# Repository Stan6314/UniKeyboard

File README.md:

UniKeyboard - Universal Keyboard
================================

The TinyBasRV and TinyBasRO microcomputers require a keyboard for writing programs and entering data. While the TinyBasRV uses a standard PC keyboard with a PS/2 connector, the TinyBasRO uses a CardKB keyboard designed for the I2C bus.

The keyboard design described here offers an alternative if you encounter any of the following problems:

*  A PS/2 keyboard for TinyBasRV is too large for your intended purpose
*  CardKB is too small (the buttons are too close together)
*  You don't have a PS/2 keyboard and can't seem to find one
*  You have the same problem with CardKB
*  You have TinyBasRV and TinyBasRO microcomputers and would like to use just one keyboard for both of them

A keyboard — for which you can find the technical documentation (circuit diagram and PCB layout) in the KiCad folder — might help you resolve any of the issues mentioned above. The documentation is in version 9.0.

In the `hw_pictures` folder, you will find images for assembling the keyboard. You can mount either 5x5 mm buttons onto the board or (with a bit of skill) 6x6 mm buttons.

The keyboard uses a simple 8-bit microcontroller—the ATtiny414 or ATtiny814—and is designed for a single-sided printed circuit board. You can connect it via an HY2.0-4P Grove connector or a 4-pin female header. Alternatively, you can populate the board with both connectors:

The source code for programming the microcontroller's FLASH memory can be found in the `src` folder. It contains source programs for both Arduino (with the `megaTinyCore` library installed) and the standalone AVR-GCC compiler.

Once the microcontroller's FLASH memory has been programmed, the keyboard will operate in one of three modes:

------------------------------------------
1) UART keypad (flashes blue upon startup)

If you connect the output connector as shown in the illustration 

The keyboard will transmit data like a UART transmitter at a speed of 9600 baud, 8 bits, no parity. It can be used in various devices for entering data and commands.

----------------------------------------
2) I2C keypad (flashes red upon startup)

When connecting the keyboard according to 

the keyboard will behave like a CardKB for TinyBasRO.

---------------------------------------------
3) PS/2 keyboard (flashes green upon startup)

When connected according to the diagram and with the short R43 on the printed circuit board connected:

The keyboard will operate in PS/2 mode for TinyBasRV. Please note that in this mode, it does not respond to the initial query from the PC during the BIOS self-test. If connected to a PC, it would only establish communication if the original keyboard were removed after startup and this keyboard were subsequently connected. It will work perfectly fine with TinyBasRV; you will simply need to construct the necessary cable.

---------------------------------------------
UniKeyboard can help you if you encounter a problem with the keyboard for TinyBas microcomputers.

* * *

Univerzální klávesnice UniKeyboard
==================================

Mikropočítače TinyBasRV a TinyBasRO potřebují pro psaní programu a zadávání dat klávesnici. Zatímco u TinyBasRV je to standardní PC klávesnice s konektorem PS/2, u TinyBasRO jde o klávesnici CardKB pro sběrnici I2C.

Zde popsaná konstrukce klávesnice vám přináší alternativu, pokud narazíte na některý z problémů:

*  PS/2 klávesnice pro TinyBasRV je příliš velká pro váš záměr
*  CardKB je příliš malá (tlačítka má moc blízko sebe)
*  PS/2 klávesnici nemáte a nedaří se ji sehnat
*  Stejný problém máte u CardKB
*  Máte oba mikropočítače a chtěli byste mít pro ně jen jednu klávesnici

S řešením některého z výše uvedených problémů by vám mohla pomoci klávesnice, jejíž technické podklady (schéma zapojení a plošný spoj) najdete ve složce `KiCad`. Podklady jsou ve verzi 9.0.

Ve složce `hw_pictures` najdete obrázky pro sestavení klávesnice. Na desku je možné osadit buď tlačítka o velikosti 5x5 mm nebo (při troše šikovnosti) tlačítka 6x6 mm.

Klávesnice používá jednoduchý osmibitový mikrořadič ATtiny414 nebo ATtiny814 a je navržena pro jednostranný plošný spoj. Můžete ji připojit přes HY2.0-4P Grove konektor nebo přes čtyřvodičový female pin strips. Případně můžete na desku osadit oba konektory:

Zdrojový kód pro naprogramování FLASH paměti mikrořadiče najdete ve složce `src`. Jsou zde uvedeny zdrojové programy jak pro Arduino s nainstalovanou knihovnou `megaTinyCore`, tak pro čistý překladač AVR-GCC.

Po naprogramování FLASH paměti mikrořadiče bude klávesnice pracovat v jednom ze tří režimů:

-------------------------------------------
1) Klávesnice UART (po startu blikne modře)

Zapojíte-li výstupní konektor podle obrázku 

bude klávesnice posílat data jako UART vysílač rychlostí 9600 Bd, 8 bitů, bez parity. Lze ji využít v různých zařízeních na vkládání dat a povelů.

--------------------------------------------
2) Klávesnice I2C (po startu blikne červeně)

Při zapojení klávesnice podle 

se bude klávesnice chovat jako CardKB pro TinyBasRO.

-------------------------------------------
3) Klávesnice PS/2 (po startu blikne zeleně)

Při zapojení podle obrázku a propojení spojky na plošném spoji:

Klávesnice bude pracovat v režimu PS/2 pro TinyBasRV. Pozor na to, že v tomto režimu neodpovídá na úvodní dotaz z PC v rámci testu, který provádí BIOS. S PC by komunikovala až po vytažení originální klávesnice po startu a teprve pak po jejím dodatečném připojení. S TinyBasRV bude komunikovat zcela bez problémů, jenom si musíte vyrobit potřebný kabel.

---------------------------------------------
UniKeyboard vám může pomoci, pokud budete mít problém s klávesnicí pro mikropočítače TinyBas.

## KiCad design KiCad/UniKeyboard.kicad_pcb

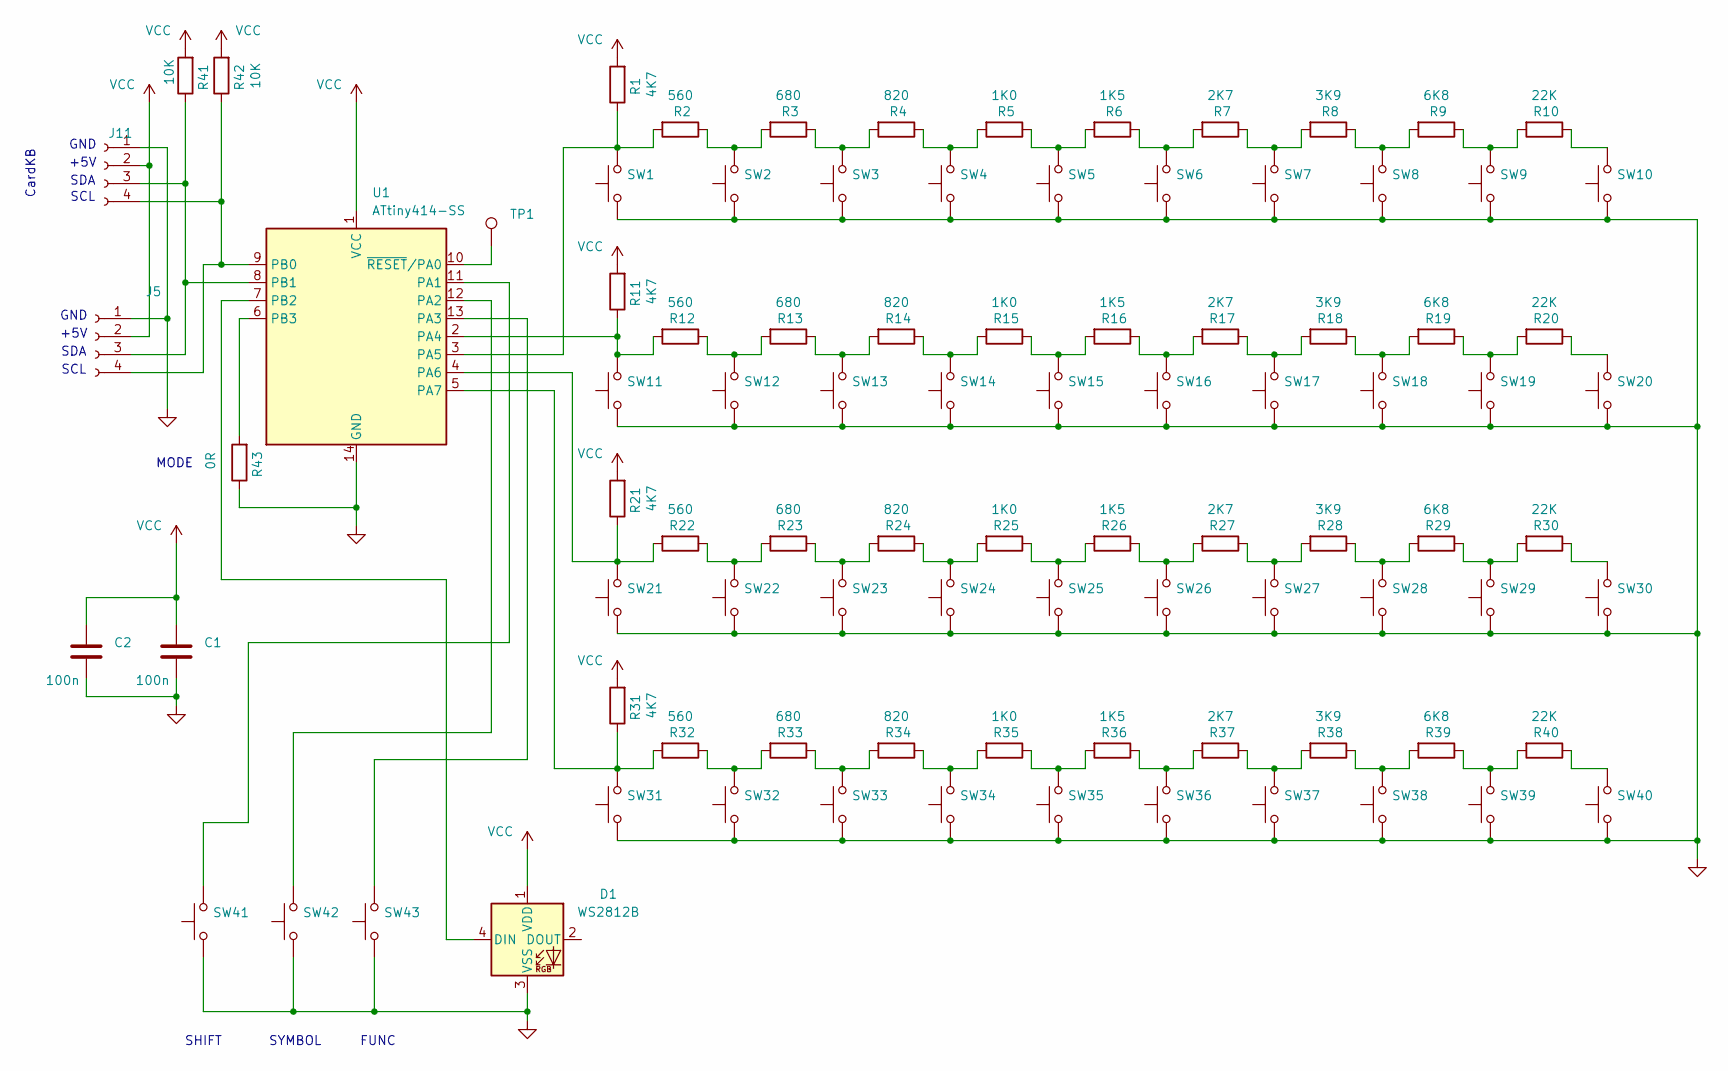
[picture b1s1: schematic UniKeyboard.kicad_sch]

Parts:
C1, C2: 100n; C_0805_2012Metric_Pad1.18x1.45mm_HandSolder
D1: WS2812B; LED_WS2812B_PLCC4_5.0x5.0mm_P3.2mm
J5: Conn_01x04_Socket; PinSocket_1x04_P2.54mm_Horizontal
J11: Conn_01x04_Socket; PinSocket_1x04_P2.00mm_Vertical
R1, R11, R21, R31: 4K7; R_1206_3216Metric_Pad1.30x1.75mm_HandSolder
R2, R12, R22, R32: 560; R_0805_2012Metric_Pad1.20x1.40mm_HandSolder
R3, R13, R23, R33: 680; R_0805_2012Metric_Pad1.20x1.40mm_HandSolder
R4, R14, R24, R34: 820; R_0805_2012Metric_Pad1.20x1.40mm_HandSolder
R5, R15, R25, R35: 1K0; R_0805_2012Metric_Pad1.20x1.40mm_HandSolder
R6, R16, R26, R36: 1K5; R_0805_2012Metric_Pad1.20x1.40mm_HandSolder
R7, R17, R27, R37: 2K7; R_0805_2012Metric_Pad1.20x1.40mm_HandSolder
R8, R18, R28, R38: 3K9; R_0805_2012Metric_Pad1.20x1.40mm_HandSolder
R9, R19, R29, R39: 6K8; R_0805_2012Metric_Pad1.20x1.40mm_HandSolder
R10, R20, R30, R40: 22K; R_0805_2012Metric_Pad1.20x1.40mm_HandSolder
R41, R42: 10K; R_1206_3216Metric_Pad1.30x1.75mm_HandSolder
R43: 0R; R_0805_2012Metric_Pad1.20x1.40mm_HandSolder
SW1, SW2, SW3, SW4, SW5, SW6, SW7, SW8, SW9, SW10, SW11, SW12, SW13, SW14, SW15, SW16, SW17, SW18, SW19, SW20, SW21, SW22, SW23, SW24, SW25, SW26, SW27, SW28, SW29, SW30, SW31, SW32, SW33, SW34, SW35, SW36, SW37, SW38, SW39, SW40, SW41, SW42, SW43: SW_Push; SW_Push_1P1T_NO_CK_KSC6xxJ
TP1: TestPoint; TestPoint_Pad_1.5x1.5mm
U1: ATtiny414-SS; SOIC-14_3.9x8.7mm_P1.27mm

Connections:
GND: C1.2, C2.2, D1.3 (VSS), J5.1, J11.1, R43.1, SW1.1, SW2.1, SW3.1, SW4.1, SW5.1, SW6.1, SW7.1, SW8.1, SW9.1, SW10.1, SW11.1, SW12.1, SW13.1, SW14.1, SW15.1, SW16.1, SW17.1, SW18.1, SW19.1, SW20.1, SW21.1, SW22.1, SW23.1, SW24.1, SW25.1, SW26.1, SW27.1, SW28.1, SW29.1, SW30.1, SW31.1, SW32.1, SW33.1, SW34.1, SW35.1, SW36.1, SW37.1, SW38.1, SW39.1, SW40.1, SW41.1, SW42.1, SW43.1, U1.14 (GND)
unnamed: D1.4 (DIN), U1.7 (PB2)
unnamed: J5.3, J11.3, R41.1, U1.8 (PB1)
unnamed: J5.4, J11.4, R42.1, U1.9 (PB0)
unnamed: R2.1, R3.2, SW2.2
unnamed: R3.1, R4.2, SW3.2
unnamed: R4.1, R5.2, SW4.2
unnamed: R5.1, R6.2, SW5.2
unnamed: R6.1, R7.2, SW6.2
unnamed: R7.1, R8.2, SW7.2
unnamed: R8.1, R9.2, SW8.2
unnamed: R10.1, SW10.2
unnamed: R9.1, R10.2, SW9.2
unnamed: R12.1, R13.2, SW12.2
unnamed: R13.1, R14.2, SW13.2
unnamed: R14.1, R15.2, SW14.2
unnamed: R15.1, R16.2, SW15.2
unnamed: R16.1, R17.2, SW16.2
unnamed: R17.1, R18.2, SW17.2
unnamed: R18.1, R19.2, SW18.2
unnamed: R19.1, R20.2, SW19.2
unnamed: R20.1, SW20.2
unnamed: R22.1, R23.2, SW22.2
unnamed: R23.1, R24.2, SW23.2
unnamed: R24.1, R25.2, SW24.2
unnamed: R25.1, R26.2, SW25.2
unnamed: R26.1, R27.2, SW26.2
unnamed: R27.1, R28.2, SW27.2
unnamed: R28.1, R29.2, SW28.2
unnamed: R29.1, R30.2, SW29.2
unnamed: R30.1, SW30.2
unnamed: R32.1, R33.2, SW32.2
unnamed: R33.1, R34.2, SW33.2
unnamed: R34.1, R35.2, SW34.2
unnamed: R35.1, R36.2, SW35.2
unnamed: R36.1, R37.2, SW36.2
unnamed: R37.1, R38.2, SW37.2
unnamed: R38.1, R39.2, SW38.2
unnamed: R39.1, R40.2, SW39.2
unnamed: R40.1, SW40.2
unnamed: SW41.2, U1.11 (PA1)
unnamed: SW42.2, U1.12 (PA2)
unnamed: SW43.2, U1.13 (PA3)
unnamed: R11.1, R12.2, SW11.2, U1.2 (PA4)
unnamed: R1.1, R2.2, SW1.2, U1.3 (PA5)
unnamed: R21.1, R22.2, SW21.2, U1.4 (PA6)
unnamed: R31.1, R32.2, SW31.2, U1.5 (PA7)
unnamed: R43.2, U1.6 (PB3)
unnamed: TP1.1, U1.10 (~RESET/PA0)
VCC: C1.1, C2.1, D1.1 (VDD), J5.2, J11.2, R1.2, R11.2, R21.2, R31.2, R41.2, R42.2, U1.1 (VCC)

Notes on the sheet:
CardKB
+5V
SHIFT
FUNC
GND
SCL
MODE
SDA
SYMBOL

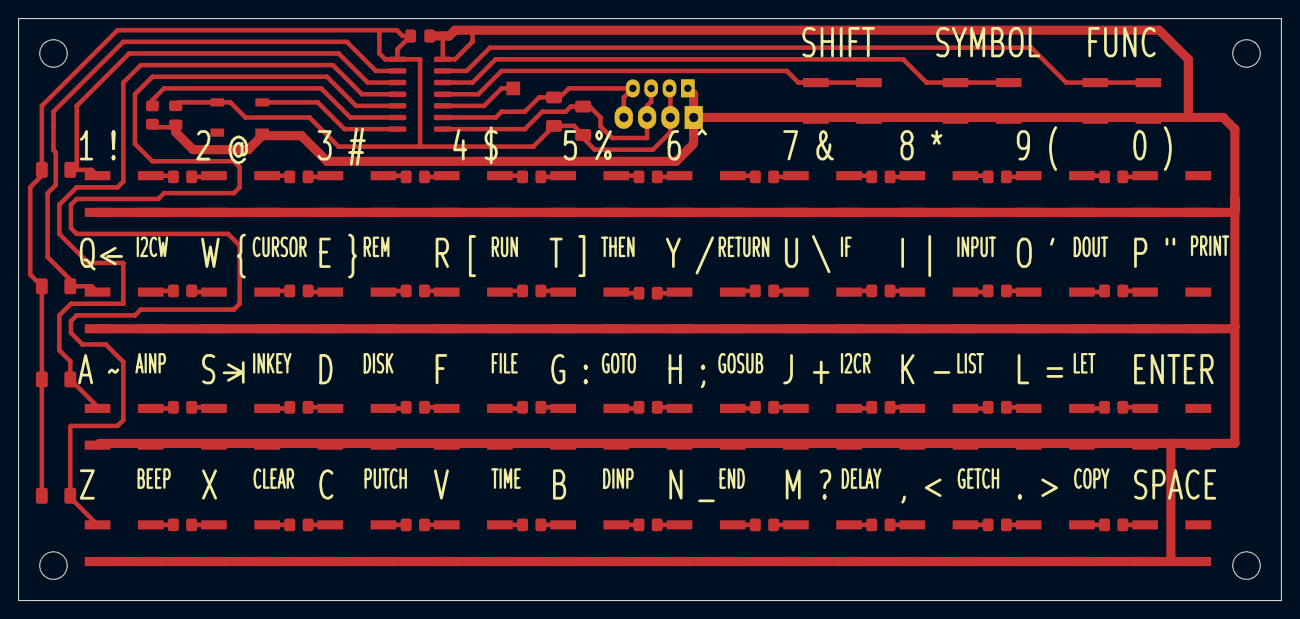
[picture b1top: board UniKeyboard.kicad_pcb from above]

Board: 2 copper layers, 137.8 x 63.5 mm, 93 parts (0 on the bottom side), 50 nets.

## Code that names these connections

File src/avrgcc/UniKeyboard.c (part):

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 * I2C, PS/2, UART Keyboard for ATtiny414 or 814
 *
 * Pin connections:
 * PB1 -> PS/2 DATA, SDA, UART TX (requires an external pull-up resistor, e.g., 4.7 kΩ to 5V)
 * PB0 -> PS/2 CLOCK, SCL (requires an external pull-up resistor, e.g., 4.7 kΩ to 5V)
 *
 * A short blink after startup indicates keyboard mode:
 * BLUE - Connecting CLOCK to GND will set UART mode (9600 Bd, 8bits, No parity)
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 * Low level hardware helpers for ATtiny414/814
 *
 * Pin connections:
 * PB0 -> PS/2 CLOCK, SCL
 * PB1 -> PS/2 DATA, SDA, UART TX
 * PB2 -> WS2812B data
 * PB3 -> MODE pin
 * PA0 -> for UPDI
 * PA1, PA2, PA3 -> SHIFT, SYMBOL, FUNC keys
 * PA5, PA4, PA6, PA7 -> analog inputs of the key matrix
 */

// PORTB pins
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  }
}

// Sets the color of a single WS2812B LED on PB2 (pin has to be an output) 
void setWS2812_Single(uint8_t rbyte, uint8_t gbyte, uint8_t bbyte)
{
  // The WS2812B requires the data order: Green, Red, Blue.
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//   Functions for keyboard matrix
// *********************************

// Analog inputs of the key matrix (PA5, PA4, PA6, PA7)
const uint8_t analogPins[] PROGMEM = {ADC_MUXPOS_AIN5_gc, ADC_MUXPOS_AIN4_gc, ADC_MUXPOS_AIN6_gc, ADC_MUXPOS_AIN7_gc};

// Debounce timing (including ms setting)
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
